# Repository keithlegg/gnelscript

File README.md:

# gnelscript

Python graphics tools. Anything goes. 

Its a sandbox for playing with numbers and pictures. I am writing this to learn 3D math. 
It is for fun and to be used as a platform to teach 3D math and graphics. 

If you want to do serious 3D work in python I suggest you have a look at the "trimesh" library instead.

    Organized by the following modules:
       -  math_ops         - math, vectors, matrices, the core logic of it all  
       -  point_ops        - 3D points, (polygons moved to poly_ops) 
       -  point_ops_2d     - 2d points, polygons
       -  poly_ops         - polygons, and objects, the "brains" of geometry processing
       -  obj2d            - data structure for 2D models.   Inherits all the other stuff  
       -  obj3d            - data structure for 3D models.   Inherits all the other stuff     
       -  raster_ops       - image manipulation with PIL, framebuffer  
       -  render           - brain dead simple 3D rendering, examples of using pygfx modules to build a 3D render  
       -  milling_ops      - process G-code files for CNC/CAM related stuff. Experimental. 
       -  grid_ops         - do things in a spatial grid like tesselations,etc - derived from dag_ops 

    Example files are split up by type:
       -  objects_3d          - examples of 3D rendering and 2D vector processing 
       -  examples_render     - examples of 3D rendering 
       -  selection           - examples of extracting portions of polygon geometry  
       -  vector              - examples of 3D vector processing

    Stuff you can ignore for now :
       -  examples.dag         - directed acyclic graph tools - pygfx.dag is 14 years old and needs cleanup 
       -  examples.milling     - examples of G-code related tools. CNC and CAM in the future?
       -  examples.wip         - work in progess examples 
       -  examples.objects_2d  - nothing here worth looking at 
       -  pygfx.objects_2d        - 2d is a work in progress - it will behave like all the 3D code but in 2D 
       -  pygfx.unit_tests        - not done yet 
       -  pygfx.raytrace          - someones code I imported and am considering intergrating 
       -  pygfx.dag_ops           - directed acyclic graph, first stab at a scene graph (not working yet)
       -  pygfx.render_2d         - nothing here yet, future home of 2D rendering 

Raster tools structure:

    |-raster_op          - wrapper around PIL to work on whole images
        |                   
        |
        |---pixel_op     - operations at pixel level - this is the .fb framebuffer used almost everywhere

3D objects structure:

    can be used along side numpy or standalone
    inside the __init__ file there is a global NUMPY_IS_LOADED to enable/disable the components that use numpy 

    The object inheritance of a gnelscript 3D object is as follows:
    
    |-math_util - standalone math tools , the first prototype for math ops and all the others  

    |-math_ops           - just what it says. Vectors, Matricies, all the boring math stuff that everything is built on
       |-point_ops       - functions to work with coordinates directly
          |-polygon_ops     - deals with polygon indices, point indices 
              |             - geometry is stored as vertex arrays and face indexes with a flat data structure  
              |-object3d    - deals with groups of polygons, normals, polygon operators loading, saving, ect 

Designed to be a self contained python module that you import into other places.

I am looking at adding other libraries like numpy, trimesh, shapely and networkx 

To enable other libraries go to __init__ and set 

[LIBRARY]_IS_LOADED =True

To use examples - just imort them like this 

    from gnelscript.examples.2d import *
    from gnelscript.examples.3d import *
    from gnelscript.examples.raster import *
    from gnelscript.examples.vector import *
    from gnelscript.examples.selection import *

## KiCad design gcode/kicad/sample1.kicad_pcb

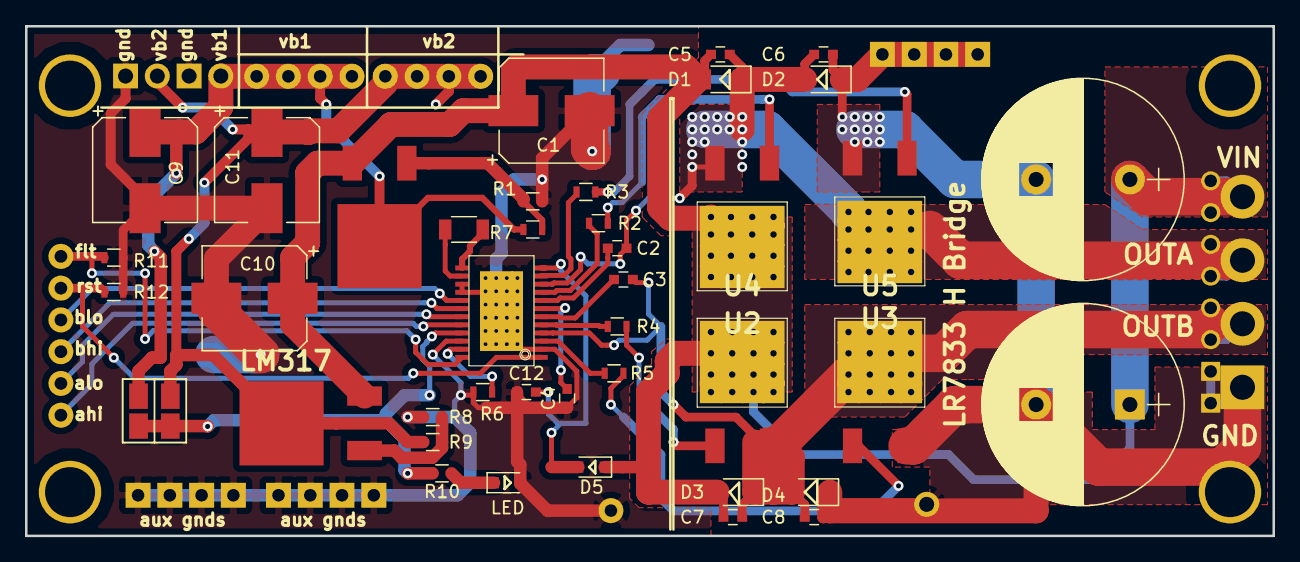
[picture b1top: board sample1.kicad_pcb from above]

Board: 2 copper layers, 99.8 x 40.8 mm, 34 parts (0 on the bottom side), 14 nets.

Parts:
C1, C9, C10, C11: CP_Elec_8x5.4
C2, C3, C4, C5, C6, C7, C8: C_0603
C12: bc; C_0603
D1, D2, D3, D4: D_1206
D5: D_0805
LED: D_0805
R1: R390; R_0603
R2, R4, R5, R6, R8, R9, R10, R11, R12: R_0603
R3: R; R_0603
R7: R240; R_0603
U2, U3, U4: DPak_TO252AA_thermals
U5: LR7833 H Bridge; DPak_TO252AA_thermals

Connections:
/out_a: C2.2, C5.2, C6.1, D1.1, D2.2, U2.3, U3.4
/out_b: C3.2, C7.2, C8.1, D3.1, D4.2, U4.3, U5.4
/vbus1: C9.1, R7.1
/vbus2: C11.1, R9.1
/vmot: C1.1, C5.1, C7.1, C10.1, D1.2, D3.2, D5.1, U2.4, U4.4
GND: C1.2, C4.1, C6.2, C8.2, C9.2, C10.2, C11.2, C12.1, D2.1, D4.1, LED.2, R1.2, R6.1, R8.2, R11.2, R12.2, U3.3, U5.3
unnamed: C12.2, D5.2
unnamed: LED.1, R10.1
unnamed: R1.1, R7.2
unnamed: R2.2, U2.1
unnamed: R3.2, U3.1
unnamed: R4.2, U4.1
unnamed: R5.2, U5.1
unnamed: R8.1, R9.2

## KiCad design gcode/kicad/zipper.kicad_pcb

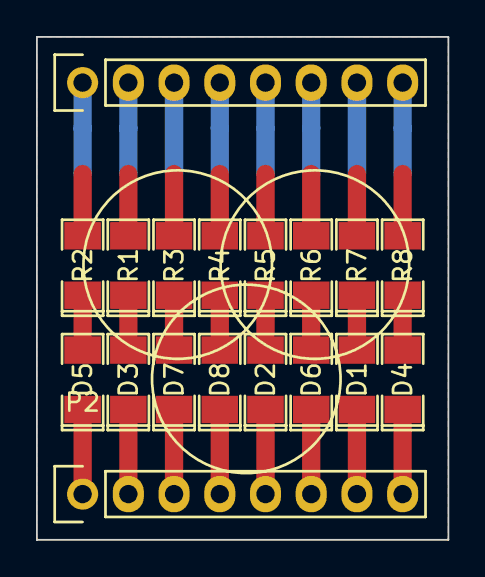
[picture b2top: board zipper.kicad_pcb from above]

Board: 2 copper layers, 22.9 x 27.9 mm, 17 parts (0 on the bottom side), 18 nets.

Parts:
D1, D2, D3, D4, D5, D6, D7, D8: LED; SMD-1206_Pol
P2: Socket_Strip_Straight_1x08
R1, R2, R3, R4, R5, R6, R7, R8: R; SMD-1206_Pol

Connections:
unnamed: D5.1, P2.1
unnamed: D1.2, R7.1
unnamed: D3.1, P2.2
unnamed: D7.1, P2.3
unnamed: D3.2, R1.1
unnamed: D8.1, P2.4
unnamed: D2.1, P2.5
unnamed: D5.2, R2.1
unnamed: D6.1, P2.6
unnamed: D1.1, P2.7
unnamed: D4.1, P2.8
unnamed: D7.2, R3.1
unnamed: R3.2, R6.2
unnamed: D8.2, R4.1
unnamed: R4.2, R8.2
unnamed: D2.2, R5.1
unnamed: D6.2, R6.1
unnamed: D4.2, R8.1

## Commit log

2018-10-25 test , first check in
2018-10-25 first check in
2018-10-25 removed crap
2018-10-26 changed name of pycv to pygfx added 2d render
2018-10-26 readme
2018-10-26 render cleanup
2018-10-27 cleanup and more
2018-11-01 first stab of adding spherical and polar coordinates
2018-11-02 math playground - I dont know what I am doing.
2018-11-03 adding quaternion. I dont know quaternions, so I am converting from a C library I found
2018-11-03 adding quaternion type
2018-11-03 i have a migraine. It sucks
2018-11-03 split point operators into 2d and 3d
2018-11-03 triangulate N sided polygons
2018-11-04 fixed N sided triangulate function
2018-11-04 readme edit
2018-11-04 adding polygon loft
2018-11-04 moved object3d into its own module
2018-11-05 cleanup of object module
2018-11-05 added get_edges tool
2018-11-05 added num polys as a property
2018-11-05 improved object inspection functions (normal,face,edge)
2018-11-05 cleanup of example code.
2018-11-06 redesigned the way polygons get inserted split 2D point_ops into thier own file to make more room for 3D
2018-11-06 extract faces by list of indices, and slices insert raw poly data into new objects weld multiple objects using new insert
2018-11-06 thinking about polygon face extrude, unit testing, etc
2018-11-07 selectors, idea sandbox, prim_cone, prim_arrow thinking about loft and extrude
2018-11-07 improved translate, rotate, scale of points -- make work with sub select -- intergreate point transforms with matrix -- decouple from object3d.matrix
2018-11-07 subselect rotate, transform, scale points rethink internal matrix and overall object transforms kill bugs
2018-11-08 changed load_obj/save_obj to load/save first stab at using face normal for copy SOP lookup pt index by face index
2018-11-08 polygon extrude is working!
2018-11-08 poly extrude is looking great!
2018-11-10 added concept of "geom" a psudeo geometry type with is a list of lists redesigning functiions to work with new geom type
2018-11-10 improving geometry operators to work in memory
2018-11-10 fix bug in face extrude that led to undesirable topology
2018-11-10 added numpy module disable worked on sub select
2018-11-10 numpy disable option
2018-11-11 added a sub_select method to feed IDs into other functions COPY sop testing
2018-11-11 subselect, transform subgroup of points
2018-11-12 point modifications use matrices added concept of "point groups"
2018-11-12 sorting out the geom/ptgrp/ transforms command logic
2018-11-12 test spherical coordinates back to more math
2018-11-14 adding more spherical and polar coordinate
2018-11-14 vector intersections in 2D and 3D
2018-11-15 cleanup, adding simple polygon lighting to renderer
2018-11-16 added a simple light/shadow effect to scanline render
2018-11-16 animated lights in a render
2018-11-16 cleanup, making things better. Lots to do
2018-11-17 cleanup
2018-11-17 added render lighting info -> export as object
2018-11-17 use render info to extract polygons from an object
2018-11-18 added a raytracer, cleanup up raster tools
2018-11-18 raytracer - built from someones code I found
2018-11-18 added 3D arrow model, cleanup primitive object types and interfaces to them
2018-11-19 adding matrixplayground.mel to math util
2018-11-19 cleaning up primitive objects , added 3D arrow
2018-11-21 select geometry spatially from a point
2018-11-21 fixed bug with zero indexing on face info commands
2018-11-21 select polygons by distance to a point
2018-11-22 moved examples out of unit_tests and back to examples added examples_wip
2018-11-22 split examples into multiple files
2018-11-22 added math tools in vector examples
2018-11-22 split off more example files - added example_selection
2018-11-23 2d rendering, vectors , point projection
2018-11-23 added bloody simple 2d render for vectors, and dots
2018-11-23 imrproved bloody simple renderer
2018-11-24 working on a simple 2D renderer
2018-11-24 improved objfile loader - now works with N sided faces
2018-11-24 added normals to OBJ loader , almost got UVS also
2018-11-25 fixed bug with interface to scale_pts
2018-11-26 animate a 2d render of a unit circle and right triangle
2018-11-26 animate a simple bresenham line drawing step by step
2018-11-28 added simple fractal tree
2018-11-29 adding 2X2 matrix object for 2D transforms
2018-11-29 2X2 matrix multiply testing
2018-11-29 docs
2018-11-29 more 2d examples , figuring out 2d renderer interface
2018-11-30 added 2.5D object load and save
2018-12-01 really basic tecture mapping for scanline render added raster examples
2018-12-01 basic texture mapping. I have images on triangles!
2018-12-02 added UV texture offset in image space added get_pixel wrap when out of bounds pixel is requested
2018-12-03 added lighting+textured color mode
2018-12-03 adding homogeneous coordinates, projection matrix
2018-12-03 test of image in readme
2018-12-04 got basic perspective/matrix working
2018-12-15 fixed bug in perspective renderer that would draw double lines
2018-12-17 added perspective rendering to scanline
2018-12-20 extract 3d vectors from raytracer and dump to obj file
2018-12-20 added normal vector to export from raytracer
2019-04-03 adding experimental gcode parser for milling machine
2019-04-03 gcode dialect in a dictionary
2019-04-03 adding gcode and docs
2019-04-03 more gcode parsing
2019-04-05 gcode parse
2019-04-12 gcode parsing - halfway works!
2019-04-12 gcode parsing works!!!
2019-04-24 fixed line indexing and command split
2019-04-24 added command recognition
2019-06-28 added linuxcnc parser commands
2019-07-03 adding kicad parser
2019-07-03 working on simple kicad pcb parser
2019-07-04 working on a kicad parser
2019-07-05 working on kicad to obj file
2019-07-07 kicad parser
2019-07-07 kicad parsing - added input files
2019-07-24 oops, forgot to add some files
2019-12-11 made a numpy disable switch
2019-12-12 render matrix as 3 vecs
2019-12-12 made pyrender2 a super-module of pygfx
2019-12-17 load matrix from file
2019-12-17 render matrix
2019-12-28 renamed top module
2020-01-15 changed name
2020-01-15 vertex color save
2020-01-18 adding polygon revolve
2020-01-20 added 3d bezier curve, revolve surfaces
2020-01-21 parametric surfaces
2021-03-16 added list of fids to get_face_geom()
2021-04-04 kicad import
2021-04-05 kicad and NGC file formats
2021-04-05 kicad to ngc
2021-04-13 kicad/linuxcnc import export
2021-04-14 kicad to linuxcnc is "working"
2022-11-23 test check in
2022-11-24 test of vector stuff
2022-11-24 added imagecam
2022-11-25 added geojson loader
2022-11-26 blah
2022-11-26 added 2d, 2.5d objects
2022-11-27 code cleanup
2022-12-19 added maya, blender and gnolmec linker tools
2022-12-21 blender integration
2022-12-26 adding nearest neighbor for ngc export
2022-12-26 adding grid optimizer
2022-12-27 making primitive scenegraph
2022-12-27 spatial optimizer in progress
2022-12-29 adding 2d objects
2022-12-30 added clone object to tesselator
2022-12-30 vector render
2022-12-30 vector render and json output
2022-12-31 added global translations to vectorflow
2023-01-02 added 3d path calculation
2023-01-04 3d math - intersection and extraction
2023-01-06 vector polygon intersection
2023-01-06 polygon intersection works
2023-01-07 polygon intersection tools
2023-01-08 cam stuff
2023-01-08 pesky rounding errors on matrix multiply
2023-01-08 waterline cam tool
2023-01-09 tessellator file loader
2023-01-09 cloned milling_op from vectorflow
2023-01-12 insert poly position
2023-01-23 added icosahedron primitive
2023-01-29 rewrote insert polygon, triangulate faces of object
2023-01-29 added numpy/scipy math ops, cleanup
2023-08-20 adding image crapola
2023-09-04 added json export and other stuff
2023-09-04 vector scanlines
2023-12-09 yay.. another checkin
2023-12-10 added a very basic tool to self document changed point_operator to point_operator_3d
2023-12-14 misc cleanup
2023-12-15 adding 3d printing gcode
2023-12-23 added laserGRBL gcode format
2023-12-24 added true 3d gcode
2023-12-24 gcode cleanup
2023-12-24 more cleanup
2023-12-26 fix polygon scanline
2023-12-26 added N-sided polygon scanline
2023-12-29 fixed rounding error in gcode export
2023-12-30 added polygon filter
2024-02-23 more stuff
2024-02-24 add json polygon export
2024-02-25 working on tesselator
2024-02-25 more tools
2024-03-02 more gcode and milling
2024-03-07 load gcode - semi working
2024-03-09 merged milling ops with vectorflow
2024-03-10 endless cleanup
2024-03-10 messing with shapely
2024-03-15 having a big rethink..
2024-03-15 moved polygons to separate file
2024-03-15 restructuring
2024-03-18 solved a paltry geometric dilemma
2024-03-21 slicer, buffer, spiral, more experiments
2024-03-22 build disk cache
2024-03-22 slicey dicey
2024-04-06 fixed bug in json polygon export
2024-04-14 adding tessellation
2024-04-15 added tessellation tool
2024-04-18 added buffer
2024-04-19 more matrices
2024-04-20 build extruded curve along a spline
2024-10-30 test
2025-03-07 adding gcode tools, megatron protocol
